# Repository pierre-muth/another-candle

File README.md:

# another-candle
Everything you need to build another eletronic candle

See details here :
https://pierremuth.wordpress.com/2018/01/04/another-candle/

Or here :
https://hackaday.io/project/29331-another-candle

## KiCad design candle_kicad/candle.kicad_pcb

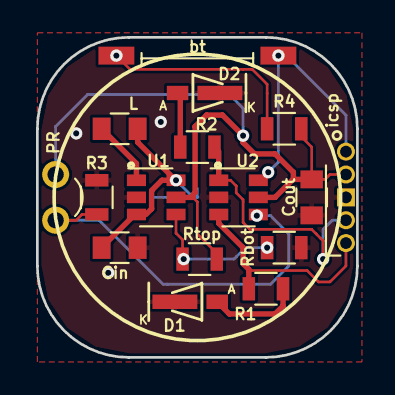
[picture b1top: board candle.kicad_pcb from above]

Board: 2 copper layers, 17.8 x 17.8 mm, 18 parts (1 on the bottom side), 12 nets.

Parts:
Cin: 4.7u; C_0805
Cout: 10u; C_0805
D1, D2: LED; VariousLED
L: 4.7u; C_0805
PR: Photores; LED_D3.0mm_FlatTop
R1, R2: R; R_0805
R3, R4: 10K; R_0805
Rbot: 309K; R_0805
Rtop: 536K; R_0805
U1: MCP1623/24; SOT-23-6
U2: PIC10F320/322; SOT-23-6
Vin +: Batt; Pin_Header_Straight_1x01_Pitch2.54mm
bt: SW_PUSH; SW_SPST_EVQPE1
icsp: PICKIT3_ICSP; Pin_Header_Straight_1x05_Pitch1.27mm
logo: LOGO

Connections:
+3V3: Cout.1, PR.1, R4.1, Rtop.1, U1.5, U2.5, icsp.2
GND: Cin.2, Cout.2, D1.1, D2.1, R3.2, Rbot.2, U1.2, U2.2, icsp.3
unnamed: Cin.1, L.2, U1.3, U1.6, Vin +.1
unnamed: D1.2, R1.1
unnamed: D2.2, R2.1
unnamed: L.1, U1.1
unnamed: PR.2, R3.1, U2.4
unnamed: R1.2, U2.3, icsp.5
unnamed: R2.2, U2.1, icsp.4
unnamed: R4.2, bt.2
unnamed: Rbot.1, Rtop.2, U1.4
unnamed: U2.6, bt.1, icsp.1

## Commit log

2017-12-31 upload PIC10F320 code
2017-12-31 upload kicad project, schematics and PCB
2017-12-31 upload 3D drawings, fusion360 project and STLs
2018-01-05 update PIC code, led pins in high-Z during sleep
